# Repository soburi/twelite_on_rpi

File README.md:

TWE-Lite on RPi
===============

What is this?
-------------
TWE-LiteをRaspberry PiのUARTに直接接続するボードです。
ラズパイのケースにそのまま収まったり、TWE-LiteRのアダプタをケチれたりするので、
Border-Routerを作るときに役に立つはずのものです。

How to use it?
--------------
[私家版jenprog](https://github.com/soburi/jenprog)
[(https://github.com/soburi/jenprog)](https://github.com/soburi/jenprog)
で書き込みができるようになっています。

* TX     - RX
* RX     - TX
* GPIO9  - SPIMISO(Programming-mode)
* GPIO23 - reset

でTWE-LiteとRaspberryPiを接続しています。

```
jenprog -c serial -t /dev/ttyS0 --rpi --spimiso-pin=9 \
--reset-pin=23 --verbose -p slip-radio.jn516x.bin
```

のようにすると、イメージの焼き込みができます。
シリアルの指定はRPi3の場合は/dev/ttyS0、RPi2/1は/dev/ttyAMA0で。

SW1はリセットに繋がっています。所謂リセットボタン。

GPIO24はSW2に接続しています。明示的に機能は割り当てていないので、
RPi側のプログラムで任意に使用できます。
* GPIO24 - SW2

LED,SWはNXPのDR1174の接続に準拠しているので、
Contikiにある`JN516x_WITH_DR1174`の設定を使うときに便利です。
* DIO2 - LED1
* DIO3 - LED2
* DIO8 - SW3

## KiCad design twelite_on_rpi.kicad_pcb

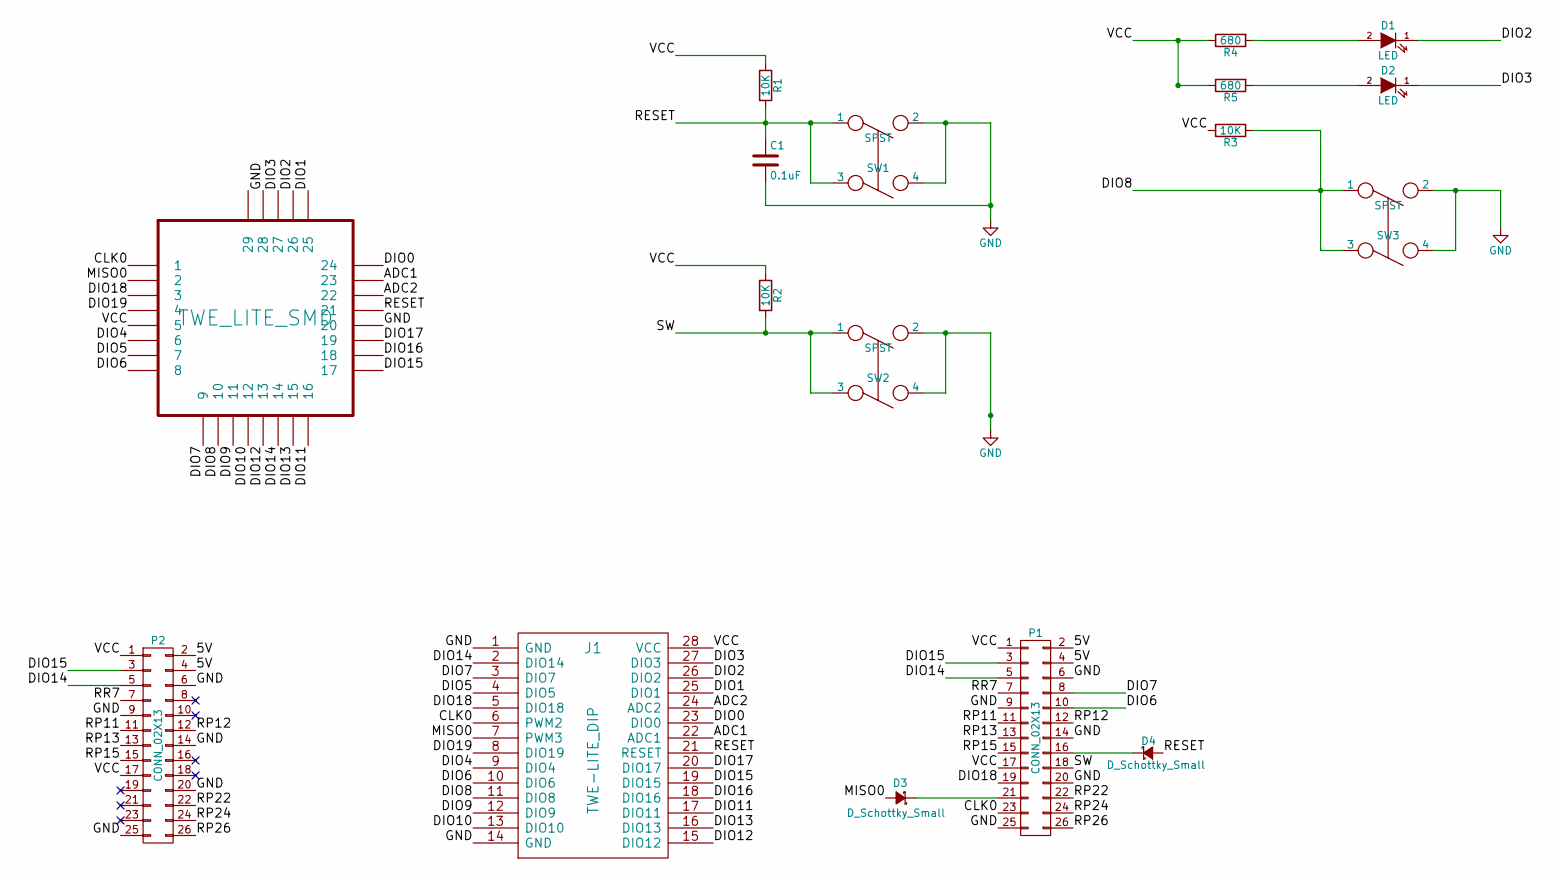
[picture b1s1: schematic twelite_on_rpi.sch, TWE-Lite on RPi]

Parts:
C1: 0.1uF; R_0603_HandSoldering
D1, D2: LED; LED-0805
D3, D4: D_Schottky_Small; R_0603_HandSoldering
J1: TWE-LITE_DIP; TWE-Lite_socket
P1, P2: CONN_02X13; Pin_Header_Straight_2x14
R1, R2, R3: 10K; R_0603_HandSoldering
R4, R5: 680; R_0603_HandSoldering
SW1, SW2, SW3: SPST; SKRPACE010
U1: TWE_LITE_SMD; TWE_LITE

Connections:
/5V: P1.2, P1.4, P2.2, P2.4
/ADC1: J1.22 (ADC1), U1.23
/ADC2: J1.24 (ADC2), U1.22
/CLK0: J1.6 (PWM2), P1.23, U1.1
/DIO0: J1.23 (DIO0), U1.24
/DIO1: J1.25 (DIO1), U1.25
/DIO2: D1.1 (K), J1.26 (DIO2), U1.26
/DIO3: D2.1 (K), J1.27 (DIO3), U1.27
/DIO4: J1.9 (DIO4), U1.6
/DIO5: J1.4 (DIO5), U1.7
/DIO6: J1.10 (DIO6), P1.10, U1.8
/DIO7: J1.3 (DIO7), P1.8, U1.9
/DIO8: J1.11 (DIO8), R3.1, SW3.1, SW3.3, U1.10
/DIO9: J1.12 (DIO9), U1.11
/DIO10: J1.13 (DIO10), U1.12
/DIO11: J1.17 (DIO11), U1.16
/DIO12: J1.15 (DIO12), U1.13
/DIO13: J1.16 (DIO13), U1.15
/DIO14: J1.2 (DIO14), P1.5, P2.5, U1.14
/DIO15: J1.19 (DIO15), P1.3, P2.3, U1.17
/DIO16: J1.18 (DIO16), U1.18
/DIO17: J1.20 (DIO17), U1.19
/DIO18: J1.5 (DIO18), P1.19, U1.3
/DIO19: J1.8 (DIO19), U1.4
/MISO0: D3.2 (A), J1.7 (PWM3), U1.2
/RESET: C1.1, D4.2 (A), J1.21 (RESET), R1.2, SW1.1, SW1.3, U1.21
/RP11: P1.11, P2.11
/RP12: P1.12, P2.12
/RP13: P1.13, P2.13
/RP15: P1.15, P2.15
/RP22: P1.22, P2.22
/RP24: P1.24, P2.24
/RP26: P1.26, P2.26
/RR7: P1.7, P2.7
/SW: P1.18, R2.2, SW2.1, SW2.3
/VCC: J1.28 (VCC), P1.1, P1.17, P2.1, P2.17, R1.1, R2.1, R3.2, R4.1, R5.1, U1.5
GND: C1.2, J1.1 (GND), J1.14 (GND), P1.6, P1.9, P1.14, P1.20, P1.25, P2.6, P2.9, P2.14, P2.20, P2.25, SW1.2, SW1.4, SW2.2, SW2.4, SW3.2, SW3.4, U1.20, U1.28
unnamed: D1.2 (A), R4.2
unnamed: D2.2 (A), R5.2
unnamed: D3.1 (K), P1.21
unnamed: D4.1 (K), P1.16

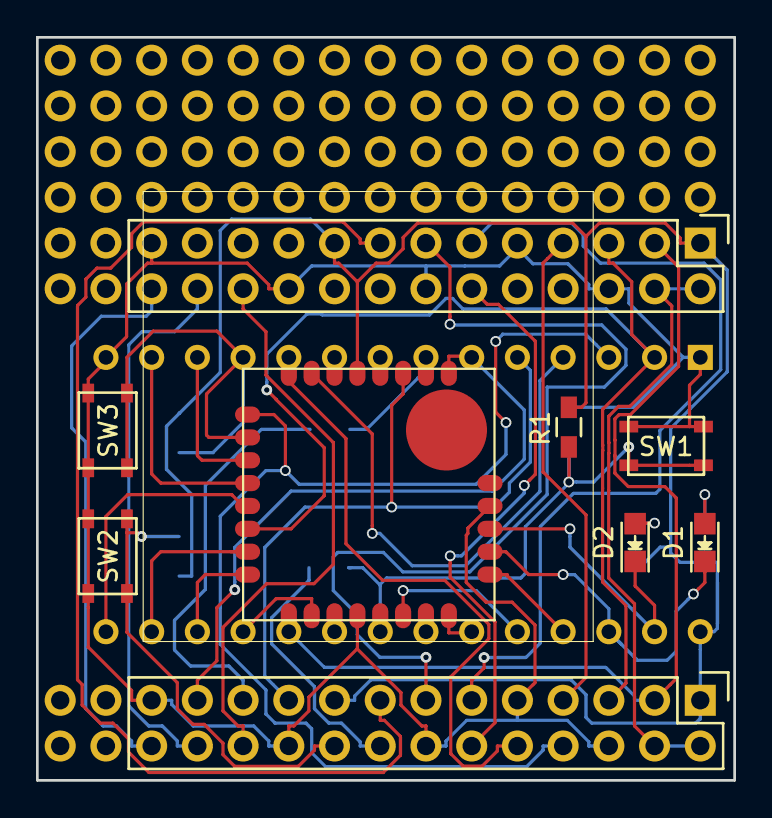
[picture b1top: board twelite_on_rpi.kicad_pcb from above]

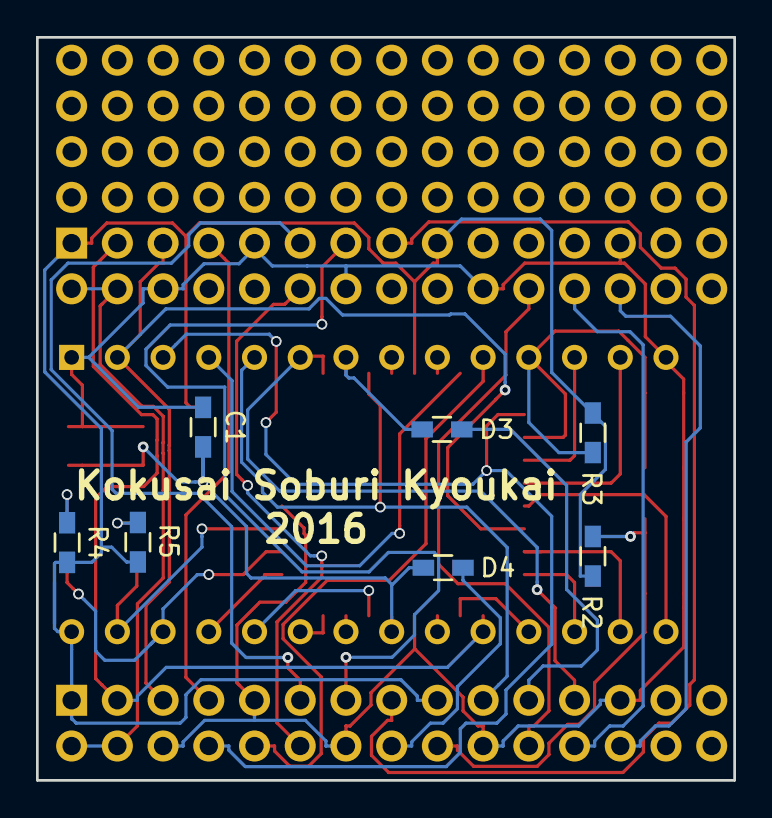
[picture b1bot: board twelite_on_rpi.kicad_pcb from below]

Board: 2 copper layers, 38.7 x 41.3 mm, 85 parts (7 on the bottom side), 41 nets.

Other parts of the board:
1, 2, 3, 4, 5, 6, 7, 8, 9, 10, 11, 12, 13, 14, 15, 16, 17, 18, 19, 20, 21, 22, 23, 24, 25, 26, 27, 28, 29, 30, 31, 32, 33, 34, 35, 36, 37, 38, 39, 40, 41, 42, 43, 44, 45, 46, 47, 48, 49, 50, 51, 52, 53, 54, 55, 56, 57, 58, 59, 60, 61, 62, 63, 64, 71, 72, 73, 74: SolderWirePad_single_Universal
